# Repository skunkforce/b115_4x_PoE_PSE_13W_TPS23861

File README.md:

# edgy_board number b115
This design is part of the [edgy board project](https://github.com/skunkforce/edgy_boards). It provides the functionality of the PoE PSE [tps23861](https://www.ti.com/lit/ds/symlink/tps23861.pdf?HQS=dis-dk-null-digikeymode-dsf-pf-null-wwe&ts=1679496827255). [view it in browser with kiCanvas](https://kicanvas.org/?github=https://github.com/skunkforce/b115_4x_PoE_PSE_13W_TPS23861/tree/master/board)

# getting started
This repository uses submodules. After cloning use the command 

```$ git submodule update --init --recursive```

to pull the submodules before opening the project with kicad. 

# Tests
Tests can be found in [TESTS.md](TESTS.md)

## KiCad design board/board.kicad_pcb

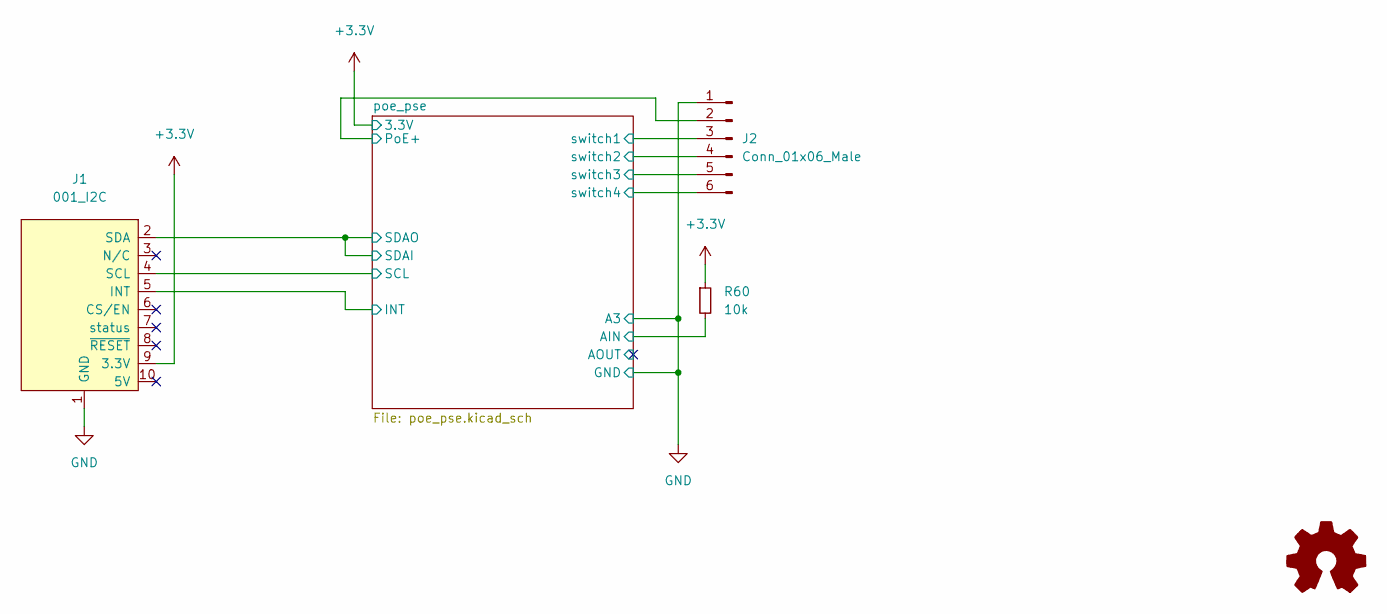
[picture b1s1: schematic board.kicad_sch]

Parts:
J1: 001_I2C; on_edge_2x05_device
J2: Conn_01x06_Male; PinHeader_1x06_P2.54mm_Vertical
LOGO1: Logo_Open_Hardware_Small; OSHW-Symbol_6.7x6mm_SilkScreen
R60: 10k; R_0402_1005Metric; lcsc C25744

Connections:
+3.3V: J1.9 (3.3V), R60.1; also elsewhere on the board
/poe_pse/AIN: R60.2; also elsewhere on the board
/poe_pse/INT: J1.5 (INT); also elsewhere on the board
/poe_pse/PoE+: J2.2; also elsewhere on the board
/poe_pse/SCL: J1.4 (SCL); also elsewhere on the board
/poe_pse/SDAI: J1.2 (SDA); also elsewhere on the board
/poe_pse/switch1: J2.3; also elsewhere on the board
/poe_pse/switch2: J2.4; also elsewhere on the board
/poe_pse/switch3: J2.5; also elsewhere on the board
/poe_pse/switch4: J2.6; also elsewhere on the board
GND: J1.1 (GND), J2.1; also elsewhere on the board

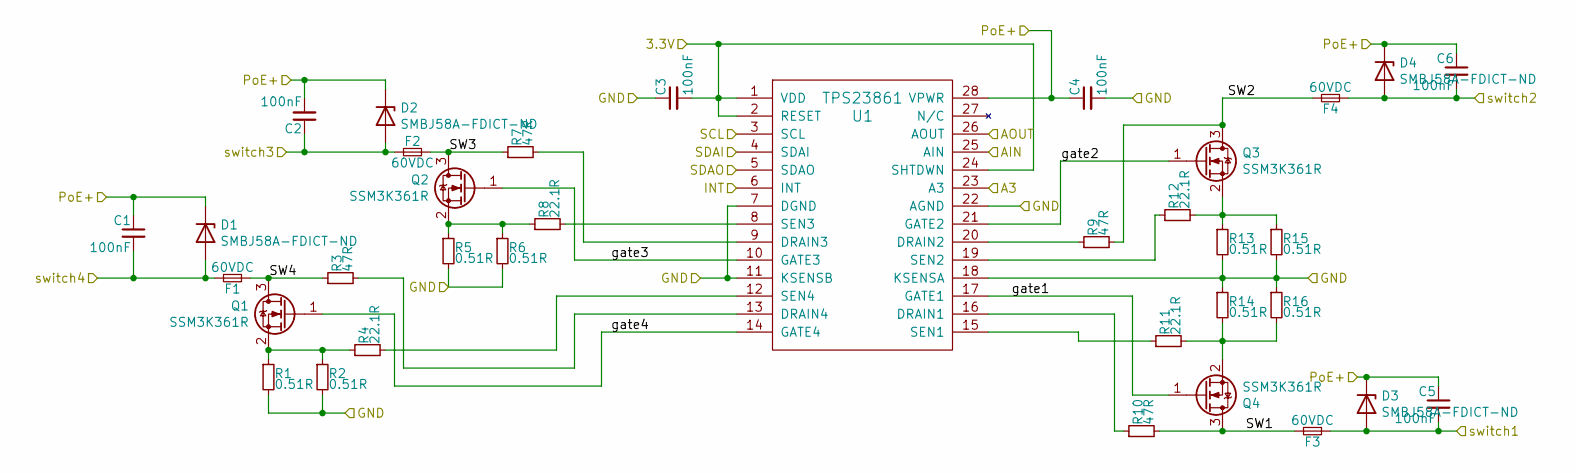
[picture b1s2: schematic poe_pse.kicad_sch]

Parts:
C1, C2, C4, C5, C6: 100nF; C_0603_1608Metric; Voltage 100V; Digi-Key_PN 1276-6807-1-ND
C3: 100nF; C_0603_1608Metric; Voltage 6.3V; Digi-Key_PN 1276-6807-1-ND
D1, D2, D3, D4: SMBJ58A-FDICT-ND; D_SMB; lcsc C157526
F1, F2, F3, F4: 60VDC; Fuse_1206_3216Metric; Digi-Key_PN F2569CT-ND
Q1, Q2, Q3, Q4: SSM3K361R; SOT-23; lcsc C5444678
R1, R2, R5, R6, R13, R14, R15, R16: 0.51R; R_0603_1608Metric; Tolerance 1%; Digi-Key_PN P.51AJCT-ND
R3, R7, R9, R10: 47R; R_0603_1608Metric; Tolerance 5%; Digi-Key_PN ‎RMCF0603JT47R0CT-ND‎
R4, R8, R11, R12: 22.1R; R_0603_1608Metric; Tolerance 1%; Digi-Key_PN P22.1HCT-ND
U1: TPS23861; TSSOP-28_4.4x9.7mm_P0.65mm; Digi-Key_PN 296-37969-5-ND

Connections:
+3.3V: C3.2, U1.1 (VDD), U1.2 (RESET), U1.24 (SHTDWN); also elsewhere on the board
/poe_pse/AIN: U1.25 (AIN); also elsewhere on the board
/poe_pse/AOUT: U1.26 (AOUT)
/poe_pse/INT: U1.6 (INT); also elsewhere on the board
/poe_pse/PoE+: C1.1, C2.2, C4.1, C5.1, C6.1, D1.1 (A1), D2.1 (A1), D3.1 (A1), D4.1 (A1), U1.28 (VPWR); also elsewhere on the board
/poe_pse/SCL: U1.3 (SCL); also elsewhere on the board
/poe_pse/SDAI: U1.4 (SDAI), U1.5 (SDAO); also elsewhere on the board
/poe_pse/SW1: F3.2, Q4.3 (D), R10.2
/poe_pse/SW2: F4.2, Q3.3 (D), R9.2
/poe_pse/SW3: F2.1, Q2.3 (D), R7.1
/poe_pse/SW4: F1.1, Q1.3 (D), R3.1
/poe_pse/gate1: Q4.1 (G), U1.17 (GATE1)
/poe_pse/gate2: Q3.1 (G), U1.21 (GATE2)
/poe_pse/gate3: Q2.1 (G), U1.10 (GATE3)
/poe_pse/gate4: Q1.1 (G), U1.14 (GATE4)
/poe_pse/switch1: C5.2, D3.2 (A2), F3.1; also elsewhere on the board
/poe_pse/switch2: C6.2, D4.2 (A2), F4.1; also elsewhere on the board
/poe_pse/switch3: C2.1, D2.2 (A2), F2.2; also elsewhere on the board
/poe_pse/switch4: C1.2, D1.2 (A2), F1.2; also elsewhere on the board
GND: C3.1, C4.2, R1.2, R2.2, R5.2, R6.2, R13.2, R14.1, R15.2, R16.1, U1.7 (DGND), U1.11 (KSENSB), U1.18 (KSENSA), U1.22 (AGND), U1.23 (A3); also elsewhere on the board
unnamed: Q1.2 (S), R1.1, R2.1, R4.1
unnamed: Q2.2 (S), R5.1, R6.1, R8.1
unnamed: Q3.2 (S), R12.2, R13.1, R15.1
unnamed: Q4.2 (S), R11.2, R14.2, R16.2
unnamed: R10.1, U1.16 (DRAIN1)
unnamed: R9.1, U1.20 (DRAIN2)
unnamed: R7.2, U1.9 (DRAIN3)
unnamed: R3.2, U1.13 (DRAIN4)
unnamed: R11.1, U1.15 (SEN1)
unnamed: R12.1, U1.19 (SEN2)
unnamed: R8.2, U1.8 (SEN3)
unnamed: R4.2, U1.12 (SEN4)

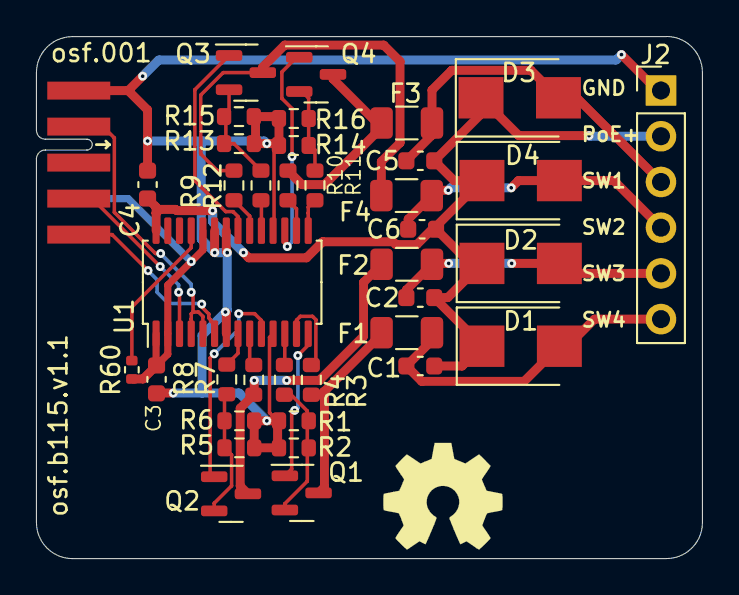
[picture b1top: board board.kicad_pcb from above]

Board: 2 copper layers, 37.0 x 29.0 mm, 39 parts (0 on the bottom side), 31 nets.

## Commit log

2023-03-27 placed and routed
2023-03-27 broke out address lines
2023-12-15 moved symbol to local library
2024-01-30 added lcsc part numbers
2026-02-04 refactored to single sided board and added AIN pull up
2026-02-04 fixed incorrect fuse strength
